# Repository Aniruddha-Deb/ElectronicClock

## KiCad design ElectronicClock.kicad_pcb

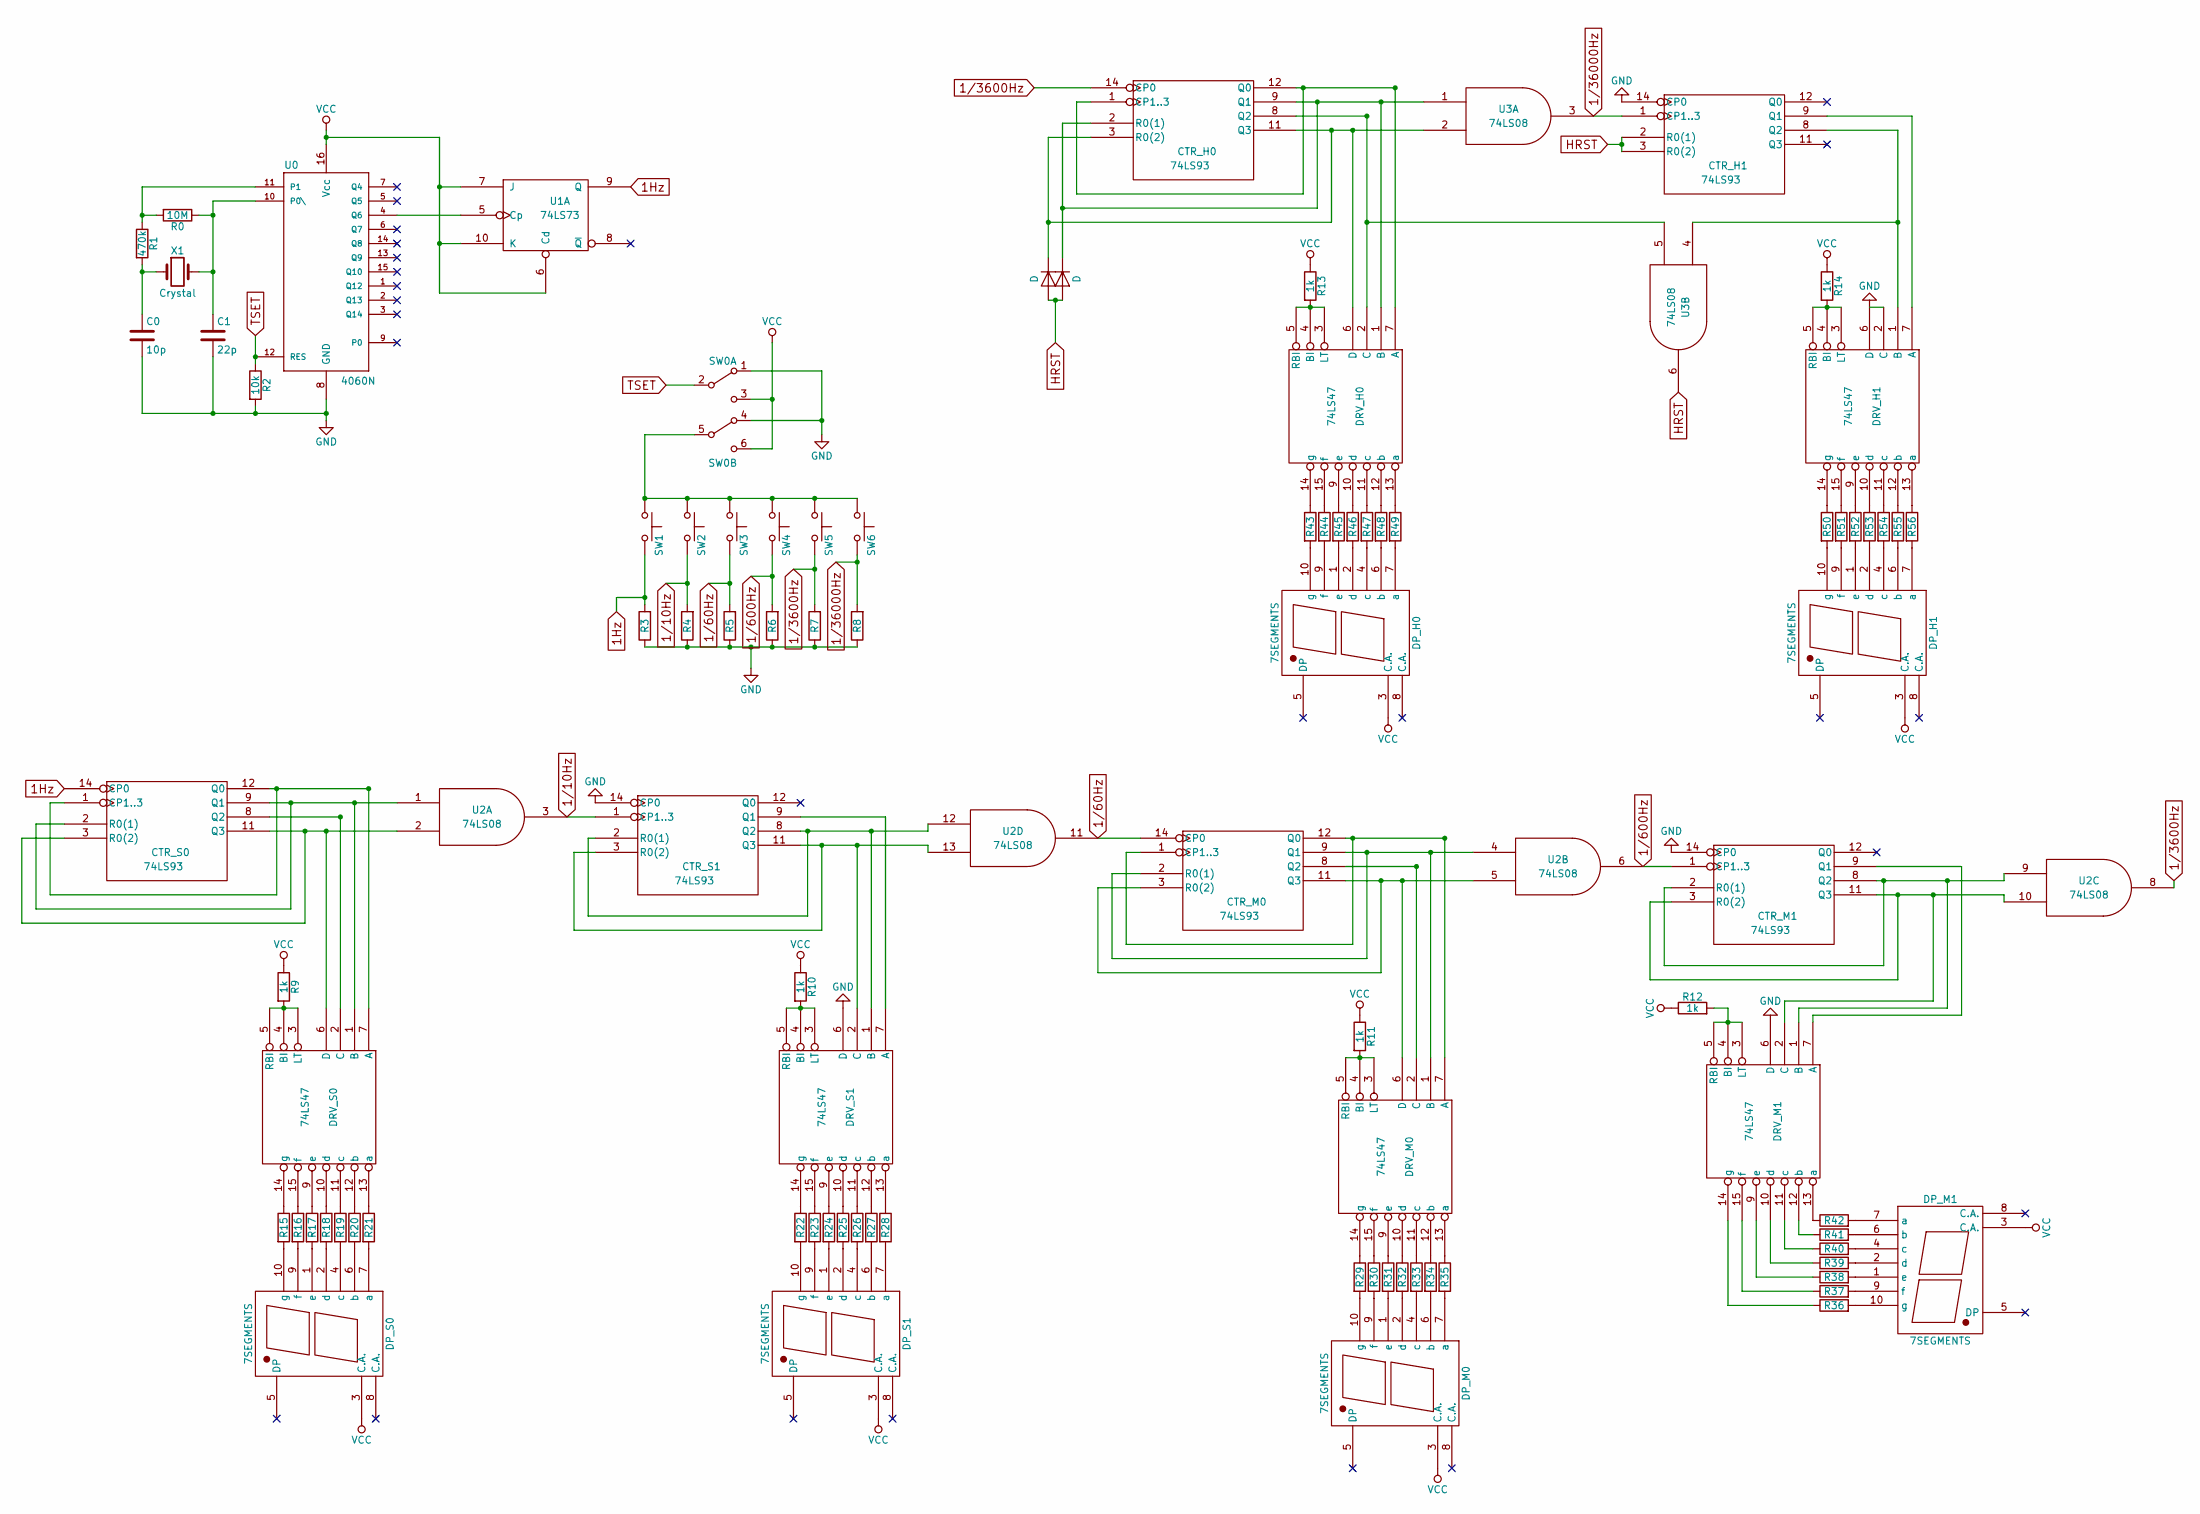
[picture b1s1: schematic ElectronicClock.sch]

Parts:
C0: 10p; C_Disc_D3.0mm_W2.0mm_P2.50mm
C1: 22p; C_Disc_D3.0mm_W2.0mm_P2.50mm
CTR_H0, CTR_H1: 74LS93; DIP-14_W7.62mm_Socket_LongPads
CTR_M0, CTR_M1: 74LS93; DIP-14_W7.62mm_Socket_LongPads
CTR_S0, CTR_S1: 74LS93; DIP-14_W7.62mm_Socket_LongPads
D1, D2: D; D_DO-41_SOD81_P7.62mm_Horizontal
DP_H0, DP_H1: 7SEGMENTS; 7SegmentLED_LTS6760_LTS6780
DP_M0, DP_M1: 7SEGMENTS; 7SegmentLED_LTS6760_LTS6780
DP_S0, DP_S1: 7SEGMENTS; 7SegmentLED_LTS6760_LTS6780
DRV_H0, DRV_H1: 74LS47; DIP-16_W7.62mm_Socket_LongPads
DRV_M0, DRV_M1: 74LS47; DIP-16_W7.62mm_Socket_LongPads
DRV_S0, DRV_S1: 74LS47; DIP-16_W7.62mm_Socket_LongPads
R0: 10M; R_Axial_DIN0204_L3.6mm_D1.6mm_P7.62mm_Horizontal
R1: 470k; R_Axial_DIN0204_L3.6mm_D1.6mm_P7.62mm_Horizontal
R2, R3, R4, R5, R6, R7, R8: 10k; R_Axial_DIN0204_L3.6mm_D1.6mm_P7.62mm_Horizontal
R9, R10, R11, R12, R13, R14, R15, R16, R17, R18, R19, R20, R21, R22, R23, R24, R25, R26, R27, R28, R29, R30, R31, R32, R33, R34, R35, R36, R37, R38, R39, R40, R41, R42, R43, R44, R45, R46, R47, R48, R49, R50, R51, R52, R53, R54, R55, R56: 1k; R_Axial_DIN0204_L3.6mm_D1.6mm_P7.62mm_Horizontal
SW0: SW_DPDT_x2; SWITCH_DPDT_8x8mm
SW1, SW2, SW3, SW4, SW5, SW6: SW_Push; SW_PUSH_6mm
U0: 4060N; DIP-16_W7.62mm_Socket_LongPads
U1: 74LS73; DIP-14_W7.62mm_Socket_LongPads
U2, U3: 74LS08; DIP-14_W7.62mm_Socket_LongPads
X1: Crystal; Crystal_DS10_d1.0mm_l4.3mm_Horizontal_1EP_style1

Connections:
1/10Hz: CTR_S1.1 (CP1..3), R4.2, SW2.2, U2.3
1/60Hz: CTR_M0.14 (CP0), R5.2, SW3.2, U2.11
1/600Hz: CTR_M1.1 (CP1..3), R6.2, SW4.2, U2.6
1/3600Hz: CTR_H0.14 (CP0), R7.2, SW5.2, U2.8
1/36000Hz: CTR_H1.1 (CP1..3), R8.2, SW6.2, U3.3
1Hz: CTR_S0.14 (CP0), R3.2, SW1.2, U1.9 (Q)
GND: C0.2, C1.2, CTR_H1.14 (CP0), CTR_M1.14 (CP0), CTR_S1.14 (CP0), DRV_H0.8 (GND), DRV_H1.2 (C), DRV_H1.6 (D), DRV_H1.8 (GND), DRV_M0.8 (GND), DRV_M1.6 (D), DRV_M1.8 (GND), DRV_S0.8 (GND), DRV_S1.6 (D), DRV_S1.8 (GND), R2.2, R3.1, R4.1, R5.1, R6.1, R7.1, R8.1, SW0.1 (A), SW0.4 (A), U0.8 (GND), U1.11 (GND), U2.7 (GND), U3.7 (GND)
HRST: CTR_H1.2 (R0(1)), CTR_H1.3 (R0(2)), D1.2 (A), D2.2 (A), U3.6
unnamed: C0.1, R1.2, X1.1
unnamed: C1.1, R0.1, U0.10 (P0\), X1.2
unnamed: CTR_H0.1 (CP1..3), CTR_H0.12 (Q0), DRV_H0.7 (A)
unnamed: CTR_H0.2 (R0(1)), CTR_H0.9 (Q1), D2.1 (K), DRV_H0.1 (B), U3.1
unnamed: CTR_H0.8 (Q2), DRV_H0.2 (C), U3.5
unnamed: CTR_H0.3 (R0(2)), CTR_H0.11 (Q3), D1.1 (K), DRV_H0.6 (D), U3.2
unnamed: CTR_H1.8 (Q2), DRV_H1.1 (B), U3.4
unnamed: CTR_H1.9 (Q1), DRV_H1.7 (A)
unnamed: CTR_M0.1 (CP1..3), CTR_M0.12 (Q0), DRV_M0.7 (A)
unnamed: CTR_M0.2 (R0(1)), CTR_M0.9 (Q1), DRV_M0.1 (B), U2.4
unnamed: CTR_M0.8 (Q2), DRV_M0.2 (C)
unnamed: CTR_M0.3 (R0(2)), CTR_M0.11 (Q3), DRV_M0.6 (D), U2.5
unnamed: CTR_M1.2 (R0(1)), CTR_M1.8 (Q2), DRV_M1.1 (B), U2.9
unnamed: CTR_M1.9 (Q1), DRV_M1.7 (A)
unnamed: CTR_M1.3 (R0(2)), CTR_M1.11 (Q3), DRV_M1.2 (C), U2.10
unnamed: CTR_S0.1 (CP1..3), CTR_S0.12 (Q0), DRV_S0.7 (A)
unnamed: CTR_S0.2 (R0(1)), CTR_S0.9 (Q1), DRV_S0.1 (B), U2.1
unnamed: CTR_S0.8 (Q2), DRV_S0.2 (C)
unnamed: CTR_S0.3 (R0(2)), CTR_S0.11 (Q3), DRV_S0.6 (D), U2.2
unnamed: CTR_S1.2 (R0(1)), CTR_S1.8 (Q2), DRV_S1.1 (B), U2.12
unnamed: CTR_S1.9 (Q1), DRV_S1.7 (A)
unnamed: CTR_S1.3 (R0(2)), CTR_S1.11 (Q3), DRV_S1.2 (C), U2.13
unnamed: DP_H0.1 (e), R45.2
unnamed: DP_H0.2 (d), R46.2
unnamed: DP_H0.4 (c), R47.2
unnamed: DP_H0.6 (b), R48.2
unnamed: DP_H0.7 (a), R49.2
unnamed: DP_H0.9 (f), R44.2
unnamed: DP_H0.10 (g), R43.2
unnamed: DP_H1.1 (e), R52.2
unnamed: DP_H1.2 (d), R53.2
unnamed: DP_H1.4 (c), R54.2
unnamed: DP_H1.6 (b), R55.2
unnamed: DP_H1.7 (a), R56.2
unnamed: DP_H1.9 (f), R51.2
unnamed: DP_H1.10 (g), R50.2
unnamed: DP_M0.1 (e), R31.2
unnamed: DP_M0.2 (d), R32.2
unnamed: DP_M0.4 (c), R33.2
unnamed: DP_M0.6 (b), R34.2
unnamed: DP_M0.7 (a), R35.2
unnamed: DP_M0.9 (f), R30.2
unnamed: DP_M0.10 (g), R29.2
unnamed: DP_M1.1 (e), R38.2
unnamed: DP_M1.2 (d), R39.2
unnamed: DP_M1.4 (c), R40.2
unnamed: DP_M1.6 (b), R41.2
unnamed: DP_M1.7 (a), R42.2
unnamed: DP_M1.9 (f), R37.2
unnamed: DP_M1.10 (g), R36.2
unnamed: DP_S0.1 (e), R17.2
unnamed: DP_S0.2 (d), R18.2
unnamed: DP_S0.4 (c), R19.2
unnamed: DP_S0.6 (b), R20.2
unnamed: DP_S0.7 (a), R21.2
unnamed: DP_S0.9 (f), R16.2
unnamed: DP_S0.10 (g), R15.2
unnamed: DP_S1.1 (e), R24.2
unnamed: DP_S1.2 (d), R25.2
unnamed: DP_S1.4 (c), R26.2
unnamed: DP_S1.6 (b), R27.2
unnamed: DP_S1.7 (a), R28.2
unnamed: DP_S1.9 (f), R23.2
unnamed: DP_S1.10 (g), R22.2
unnamed: DRV_H0.3 (LT), DRV_H0.4 (BI), DRV_H0.5 (RBI), R13.2
unnamed: DRV_H0.9 (e), R45.1
unnamed: DRV_H0.10 (d), R46.1
unnamed: DRV_H0.11 (c), R47.1
unnamed: DRV_H0.12 (b), R48.1
unnamed: DRV_H0.13 (a), R49.1
unnamed: DRV_H0.14 (g), R43.1
unnamed: DRV_H0.15 (f), R44.1
unnamed: DRV_H1.3 (LT), DRV_H1.4 (BI), DRV_H1.5 (RBI), R14.2
unnamed: DRV_H1.9 (e), R52.1
unnamed: DRV_H1.10 (d), R53.1
unnamed: DRV_H1.11 (c), R54.1
unnamed: DRV_H1.12 (b), R55.1
unnamed: DRV_H1.13 (a), R56.1
unnamed: DRV_H1.14 (g), R50.1
unnamed: DRV_H1.15 (f), R51.1
unnamed: DRV_M0.3 (LT), DRV_M0.4 (BI), DRV_M0.5 (RBI), R11.2
unnamed: DRV_M0.9 (e), R31.1
unnamed: DRV_M0.10 (d), R32.1
unnamed: DRV_M0.11 (c), R33.1
unnamed: DRV_M0.12 (b), R34.1
unnamed: DRV_M0.13 (a), R35.1
unnamed: DRV_M0.14 (g), R29.1
unnamed: DRV_M0.15 (f), R30.1
unnamed: DRV_M1.3 (LT), DRV_M1.4 (BI), DRV_M1.5 (RBI), R12.2
unnamed: DRV_M1.9 (e), R38.1
unnamed: DRV_M1.10 (d), R39.1
unnamed: DRV_M1.11 (c), R40.1
unnamed: DRV_M1.12 (b), R41.1
unnamed: DRV_M1.13 (a), R42.1
unnamed: DRV_M1.14 (g), R36.1
unnamed: DRV_M1.15 (f), R37.1
unnamed: DRV_S0.3 (LT), DRV_S0.4 (BI), DRV_S0.5 (RBI), R9.2
unnamed: DRV_S0.9 (e), R17.1
unnamed: DRV_S0.10 (d), R18.1
unnamed: DRV_S0.11 (c), R19.1
unnamed: DRV_S0.12 (b), R20.1
unnamed: DRV_S0.13 (a), R21.1
unnamed: DRV_S0.14 (g), R15.1
unnamed: DRV_S0.15 (f), R16.1
unnamed: DRV_S1.3 (LT), DRV_S1.4 (BI), DRV_S1.5 (RBI), R10.2
unnamed: DRV_S1.9 (e), R24.1
unnamed: DRV_S1.10 (d), R25.1
unnamed: DRV_S1.11 (c), R26.1
unnamed: DRV_S1.12 (b), R27.1
unnamed: DRV_S1.13 (a), R28.1
unnamed: DRV_S1.14 (g), R22.1
unnamed: DRV_S1.15 (f), R23.1
unnamed: R0.2, R1.1, U0.11 (P1)
unnamed: SW0.5 (B), SW1.1, SW2.1, SW3.1, SW4.1, SW5.1, SW6.1
unnamed: U0.4 (Q6), U1.5 (Cp)
TSET: R2.1, SW0.2 (B), U0.12 (RES)
VCC: CTR_H0.5 (VCC), CTR_H1.5 (VCC), CTR_M0.5 (VCC), CTR_M1.5 (VCC), CTR_S0.5 (VCC), CTR_S1.5 (VCC), DP_H0.3 (C.A.), DP_H1.3 (C.A.), DP_M0.3 (C.A.), DP_M1.3 (C.A.), DP_S0.3 (C.A.), DP_S1.3 (C.A.), DRV_H0.16 (VCC), DRV_H1.16 (VCC), DRV_M0.16 (VCC), DRV_M1.16 (VCC), DRV_S0.16 (VCC), DRV_S1.16 (VCC), R9.1, R10.1, R11.1, R12.1, R13.1, R14.1, SW0.3 (C), SW0.6 (C), U0.16 (Vcc), U1.4 (VCC), U1.6 (Cd), U1.7 (J), U1.10 (K), U2.14 (VCC), U3.14 (VCC)

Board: 2 copper layers, 91 parts (0 on the bottom side), 125 nets, no tracks yet.

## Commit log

2018-06-20 Added some more components
2018-06-20 Minor update
2018-06-20 Associated components with footprints
2018-06-20 Finished up the schematic, generated netlist, exported to PDF
2018-06-21 Started working on PCB
2018-06-22 Reworked the component names
2018-06-23 Routed 3 displays
